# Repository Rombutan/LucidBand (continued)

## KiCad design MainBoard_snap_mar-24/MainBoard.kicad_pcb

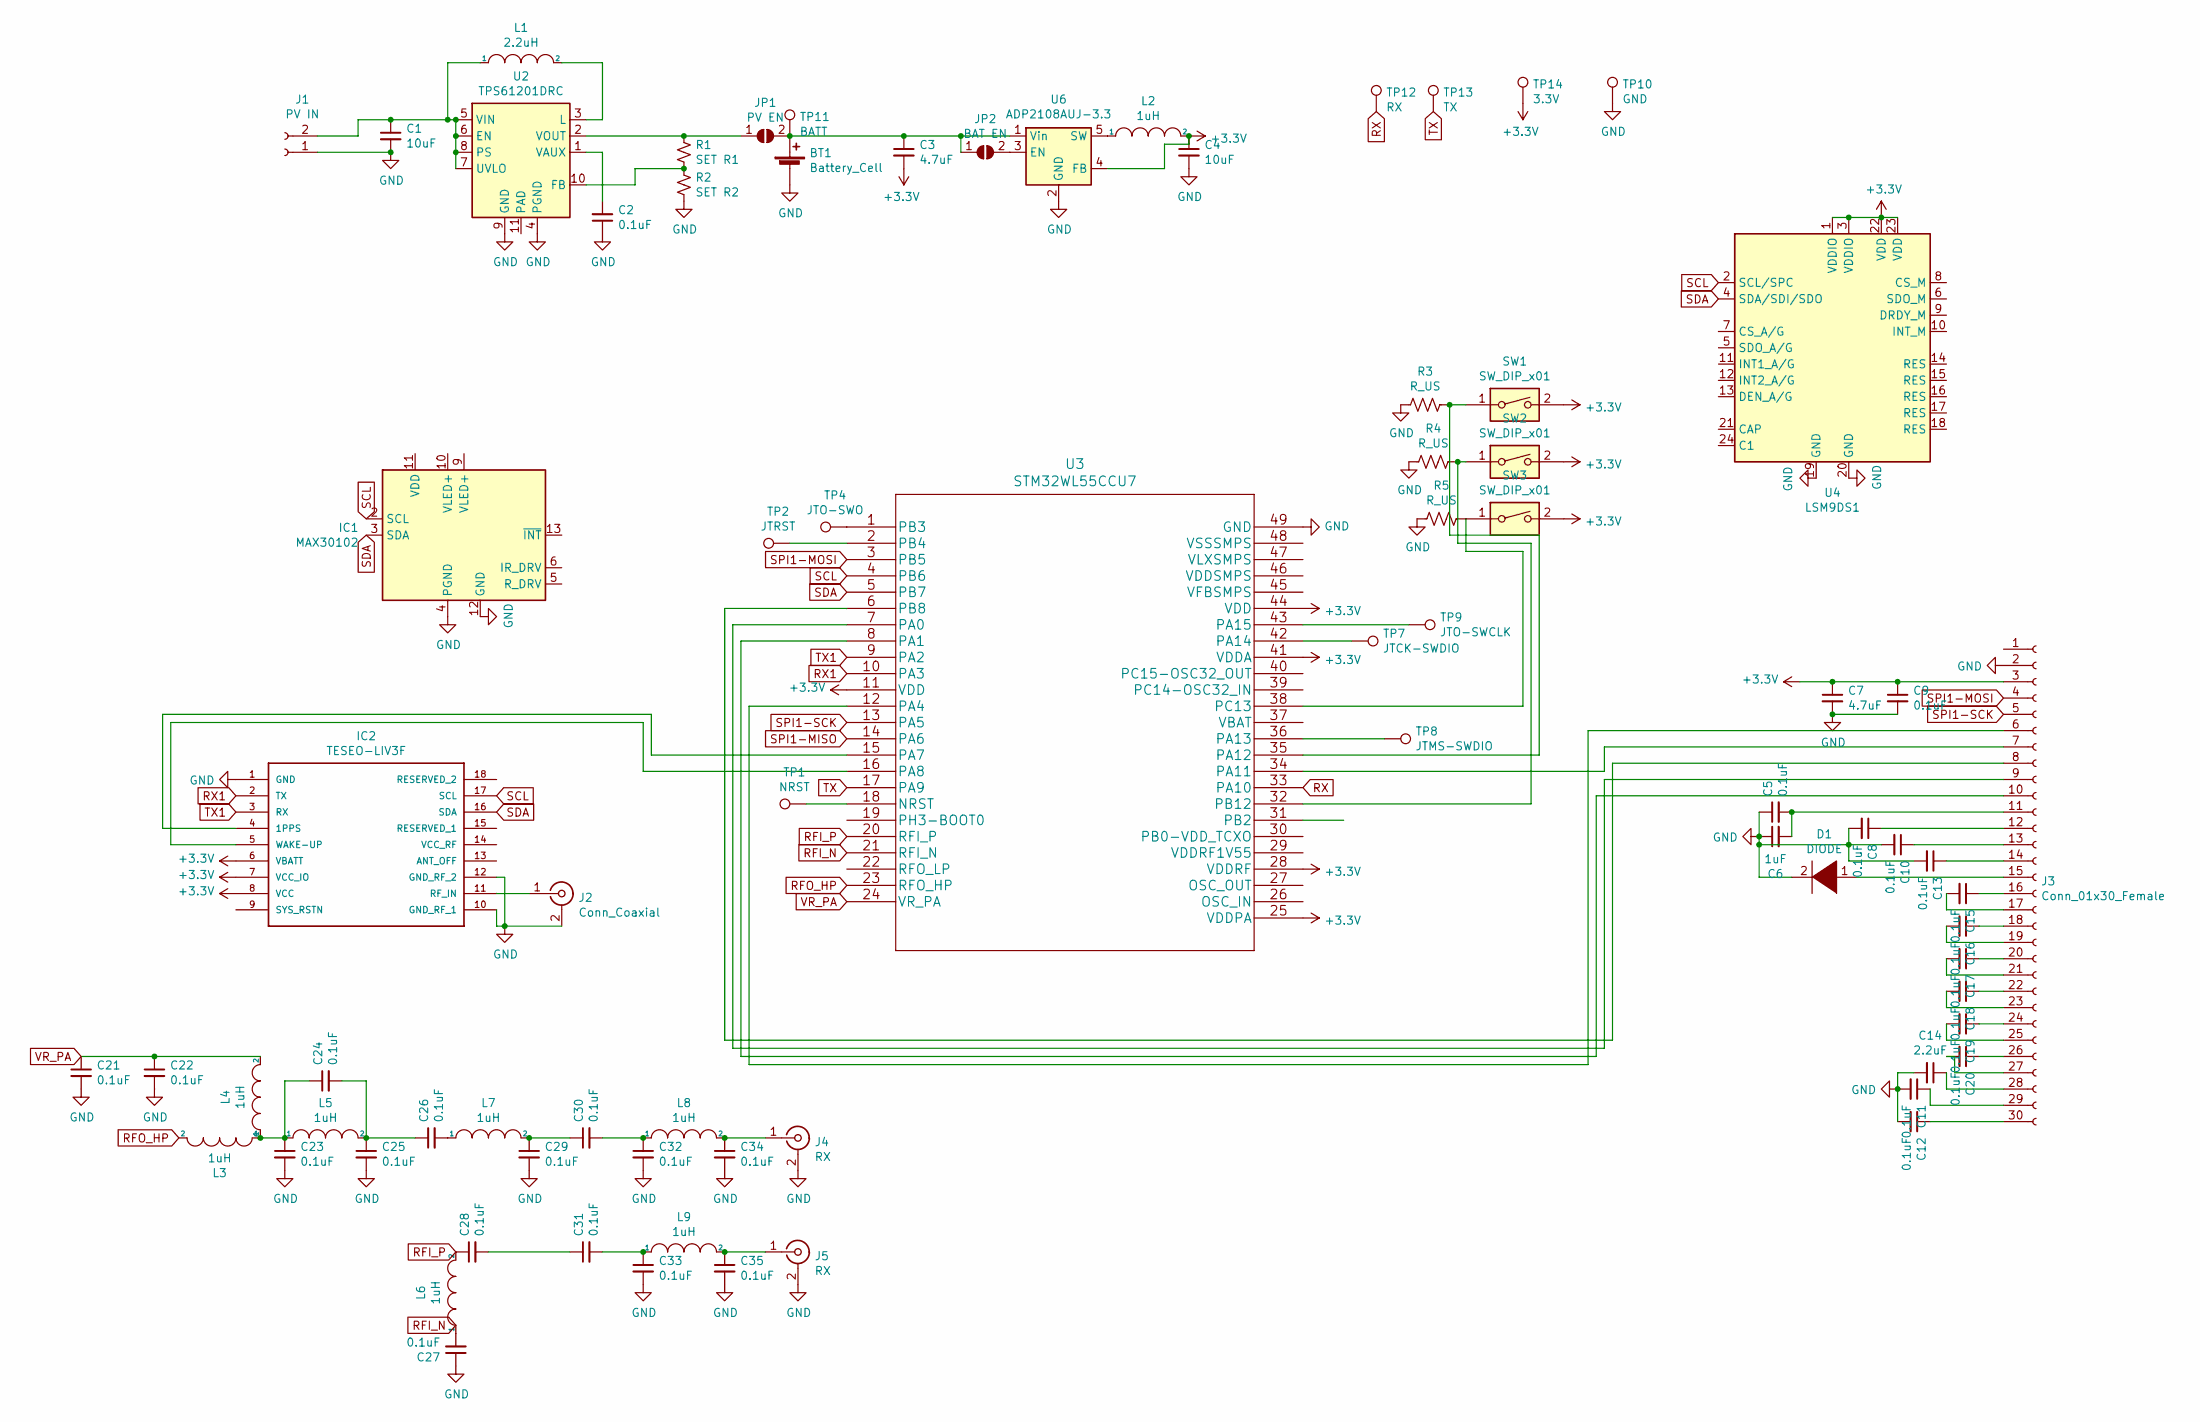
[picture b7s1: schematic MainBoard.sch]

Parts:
BT1: Battery_Cell; PinHeader_1x02_P1.00mm_Horizontal
C1, C4: 10uF; C_0402_1005Metric
C2, C5, C8, C9, C10, C11, C12, C13, C15, C16, C17, C18, C19, C20, C21, C22, C23, C24, C25, C26, C27, C28, C29, C30, C31, C32, C33, C34, C35: 0.1uF; C_0402_1005Metric
C3, C7: 4.7uF; C_0402_1005Metric
C6: 1uF; C_0402_1005Metric
C14: 2.2uF; C_0402_1005Metric
D1: DIODE; D_0402_1005Metric
IC1: MAX30102; Maxim_OLGA-14_3.3x5.6mm_P0.8mm
IC2: TESEO-LIV3F; SON110P970X1010X230-18N; MOUSER_PART_NUMBER 511-TESEO-LIV3F
J1: PV IN; PinHeader_1x02_P1.00mm_Horizontal
J2: Conn_Coaxial; U.FL_Hirose_U.FL-R-SMT-1_Vertical
J3: Conn_01x30_Female; waveshare_1.02
J4, J5: RX; U.FL_Hirose_U.FL-R-SMT-1_Vertical
JP1: PV EN; SolderJumper-2_P1.3mm_Open_RoundedPad1.0x1.5mm
JP2: BAT EN; SolderJumper-2_P1.3mm_Open_RoundedPad1.0x1.5mm
L1: 2.2uH; L_Coilcraft_LPS4018
L2: 1uH; L_Coilcraft_LPS4018
L3, L4, L5, L6, L7, L8, L9: 1uH; L_0402_1005Metric
R1: SET R1; R_0402_1005Metric
R2: SET R2; R_0402_1005Metric
R3, R4, R5: R_US; R_0402_1005Metric
SW1, SW2, SW3: SW_DIP_x01; SW_Push_1P1T-SH_NO_CK_KMR2xxG
TP1: NRST; TestPoint_Pad_2.0x2.0mm
TP2: JTRST; TestPoint_Pad_2.0x2.0mm
TP4: JTO-SWO; TestPoint_Pad_2.0x2.0mm
TP7: JTCK-SWDIO; TestPoint_Pad_2.0x2.0mm
TP8: JTMS-SWDIO; TestPoint_Pad_2.0x2.0mm
TP9: JTO-SWCLK; TestPoint_Pad_2.0x2.0mm
TP10: GND; TestPoint_Pad_2.0x2.0mm
TP11: BATT; TestPoint_Pad_2.0x2.0mm
TP12: RX; TestPoint_Pad_2.0x2.0mm
TP13: TX; TestPoint_Pad_2.0x2.0mm
TP14: 3.3V; TestPoint_Pad_2.0x2.0mm
U2: TPS61201DRC; Texas_S-PVSON-N10_ThermalVias
U3: STM32WL55CCU7
U4: LSM9DS1; LGA-24L_3x3.5mm_P0.43mm
U6: ADP2108AUJ-3.3; TSOT-23-5

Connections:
+3V3: C3.2, C4.1, C7.1, C9.1, IC2.6 (VBATT), IC2.7 (VCC_IO), IC2.8 (VCC), J3.3, L2.2, SW1.2, SW2.2, SW3.2, TP14.1, U3.11 (VDD), U3.25 (VDDPA), U3.28 (VDDRF), U3.41 (VDDA), U3.44 (VDD), U4.1 (VDDIO), U4.3 (VDDIO), U4.22 (VDD), U4.23 (VDD), U6.4 (FB)
GND: BT1.2 (-), C1.2, C2.1, C4.2, C5.1, C6.1, C7.2, C8.2, C9.2, C10.2, C11.2, C12.2, C13.2, C14.2, C21.2, C22.2, C23.2, C25.2, C27.1, C29.2, C32.2, C33.2, C34.2, C35.2, D1.2 (A), IC1.4 (PGND), IC1.12 (GND), IC2.1 (GND), IC2.10 (GND_RF_1), IC2.12 (GND_RF_2), J1.1, J2.2 (Ext), J3.2, J4.2 (Ext), J5.2 (Ext), R2.2, R3.2, R4.2, R5.2, TP10.1, U2.4 (PGND), U2.9 (GND), U3.49 (GND), U4.19 (GND), U4.20 (GND), U6.2 (GND)
unnamed: BT1.1 (+), C3.1, JP1.2 (B), JP2.1 (A), TP11.1, U6.1 (Vin)
unnamed: C1.1, J1.2, L1.1, U2.5 (VIN), U2.6 (EN), U2.7 (UVLO), U2.8 (PS)
unnamed: C2.2, U2.1 (VAUX)
unnamed: C5.2, C6.2, J3.11
unnamed: C8.1, J3.12
unnamed: C10.1, J3.13
unnamed: C11.1, J3.29
unnamed: C12.1, J3.30
unnamed: C13.1, J3.14
unnamed: C14.1, J3.28
unnamed: C15.1, J3.16
unnamed: C15.2, J3.17
unnamed: C16.1, J3.18
unnamed: C16.2, J3.19
unnamed: C17.1, J3.20
unnamed: C17.2, J3.21
unnamed: C18.1, J3.22
unnamed: C18.2, J3.23
unnamed: C19.1, J3.24
unnamed: C19.2, J3.25
unnamed: C20.1, J3.26
unnamed: C20.2, J3.27
unnamed: C23.1, C24.1, L3.1, L4.1, L5.1
unnamed: C24.2, C25.1, C26.1, L5.2
unnamed: C26.2, L7.1
unnamed: C27.2, L6.1
unnamed: C28.2, C31.1
unnamed: C29.1, C30.1, L7.2
unnamed: C30.2, C32.1, L8.1
unnamed: C31.2, C33.1, L9.1
unnamed: C34.1, J4.1 (In), L8.2
unnamed: C35.1, J5.1 (In), L9.2
unnamed: D1.1 (K), J3.15
unnamed: IC2.4 (1PPS), U3.15 (PA7)
unnamed: IC2.5 (WAKE-UP), U3.16 (PA8)
unnamed: IC2.11 (RF_IN), J2.1 (In)
unnamed: J3.6, U3.12 (PA4)
unnamed: J3.7, U3.34 (PA11)
unnamed: J3.8, U3.6 (PB8)
unnamed: J3.9, U3.7 (PA0)
unnamed: J3.10, U3.8 (PA1)
unnamed: JP1.1 (A), R1.1, U2.2 (VOUT)
unnamed: JP2.2 (B), U6.3 (EN)
unnamed: L1.2, U2.3 (L)
unnamed: L2.1, U6.5 (SW)
unnamed: R1.2, R2.1, U2.10 (FB)
unnamed: R3.1, SW1.1, U3.35 (PA12)
unnamed: R4.1, SW2.1, U3.32 (PB12)
unnamed: R5.1, SW3.1, U3.38 (PC13)
unnamed: TP1.1, U3.18 (NRST)
unnamed: TP2.1, U3.2 (PB4)
unnamed: TP4.1, U3.1 (PB3)
unnamed: TP7.1, U3.42 (PA14)
unnamed: TP8.1, U3.36 (PA13)
unnamed: TP9.1, U3.43 (PA15)
RFI_P: C28.1, L6.2, U3.20 (RFI_P)
RFO_HP: L3.2, U3.23 (RFO_HP)
RX: TP12.1, U3.33 (PA10)
RX1: IC2.2 (TX), U3.10 (PA3)
SCL: IC1.2 (SCL), IC2.17 (SCL), U3.4 (PB6), U4.2 (SCL/SPC)
SDA: IC1.3 (SDA), IC2.16 (SDA), U3.5 (PB7), U4.4 (SDA/SDI/SDO)
SPI1-MOSI: J3.4, U3.3 (PB5)
SPI1-SCK: J3.5, U3.13 (PA5)
TX: TP13.1, U3.17 (PA9)
TX1: IC2.3 (RX), U3.9 (PA2)
VR_PA: C21.1, C22.1, L4.2, U3.24 (VR_PA)

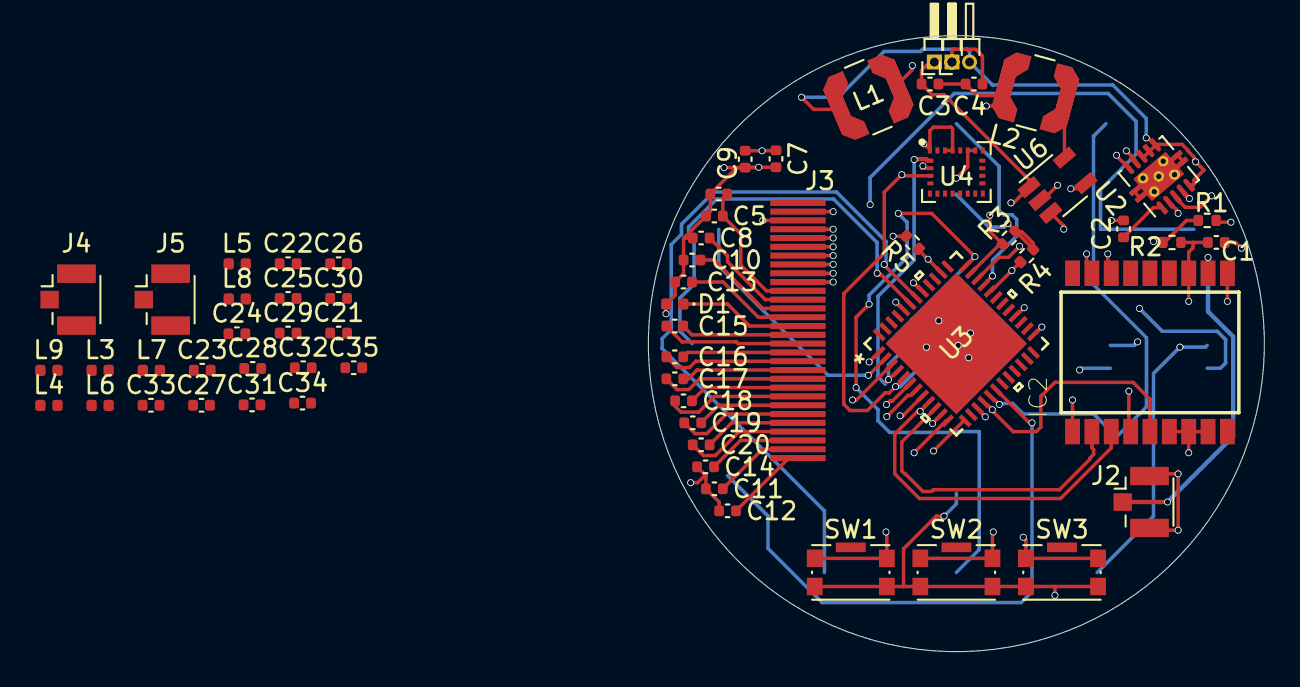
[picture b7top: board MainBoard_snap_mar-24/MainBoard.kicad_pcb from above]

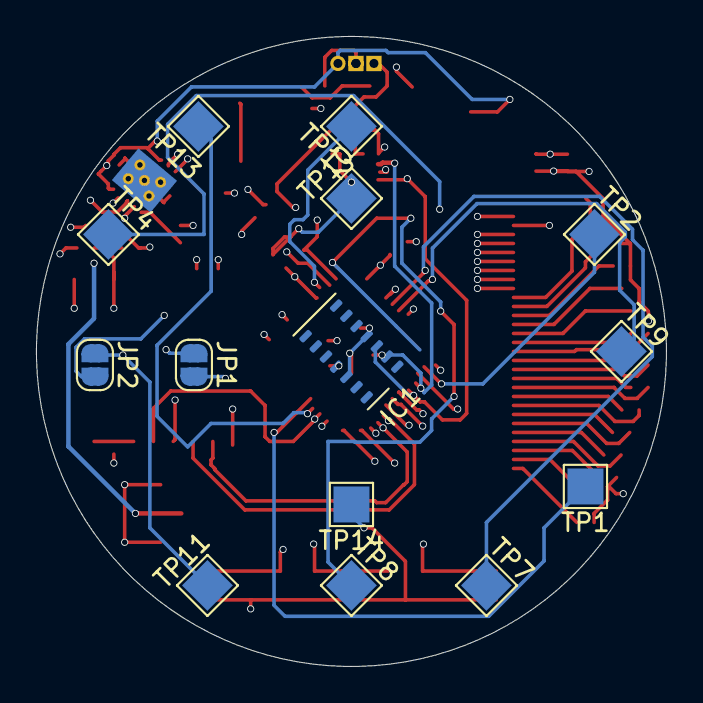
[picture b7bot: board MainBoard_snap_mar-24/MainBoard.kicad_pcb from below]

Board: 4 copper layers, 35.0 x 35.0 mm, 78 parts (14 on the bottom side), 68 nets.

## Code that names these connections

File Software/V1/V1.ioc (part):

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PA10.Mode=Asynchronous
Mcu.UserName=STM32WL55CCUx
PC14-OSC32_IN.Signal=GPIO_Output
PA3.Mode=Asynchronous
PA13.Signal=DEBUG_JTMS-SWDIO
PA9.Mode=Asynchronous
PA9.Signal=USART1_TX
PB6.Signal=I2C1_SCL
PB6.Mode=I2C
PC15-OSC32_OUT.Signal=GPIO_Input
PA1.Signal=GPIO_Output
RCC.HSE_VALUE=8000000
PB3.Mode=JTAG_5_pins
PB2.Signal=GPIO_Output
board=custom
PA15.Mode=JTAG_5_pins
PB4.Mode=JTAG_5_pins
PA14.Mode=JTAG_5_pins
PB7.Signal=I2C1_SDA
PA8.Signal=GPIO_Output
PA13.Mode=JTAG_5_pins
Mcu.Name=STM32WL55CCUx
PA2.Signal=USART2_TX
PA0.Signal=GPIO_Output
PB3.Signal=DEBUG_JTDO-SWO
PA4.Signal=GPIO_Output
Mcu.Package=UFQFPN48
PA11.Signal=GPIO_Output
PB7.Mode=I2C
PA10.Signal=USART1_RX
PA14.Signal=DEBUG_JTCK-SWCLK
PA15.Signal=DEBUG_JTDI
PB8.Signal=GPIO_Output
PA2.Mode=Asynchronous
PB4.Signal=DEBUG_JTRST
PA3.Signal=USART2_RX
PA7.Signal=GPIO_Output

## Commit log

2021-03-21 add sensors.txt
2021-03-21 add mainboard PCB files
2021-03-22 add PV supply circuit
2021-03-24 add final sensors and update PCB
2021-03-26 lots of work on PCB
2021-03-28 clean silkscreen, add power delivery, route LoRa RF
2021-03-28 add pdfs
2021-03-28 flip LoRa TX stuff to deduce footprint and track length, update pdfs
2021-03-31 ditch LoRa, switch processor to STM32WB30CE
2021-03-31 route entire damn thing in one sitting
2021-03-31 add crystal, pour ground plane
2021-05-06 many, many things :)
2021-05-06 add programming/charging dock board
2021-05-07 export gerbers
2021-05-17 remove old layout pdf
2021-05-18 add accelerometer and thicken switch traces
2021-05-18 Update images
2021-05-22 I dont even remember
2021-05-30 switch processor, add sensors, change shape'
2021-05-31 update pdf's
2021-05-31 remove old stuffs
2021-05-31 update images for README
2021-05-31 oops! I forgot the buzzer
2021-06-04 route board
2021-06-04 update 3d image
2023-01-05 make readme and decide hardware
2023-01-05 fix list in README
2023-01-05 goofy submodule won't die
2023-01-05 init pcb commit
2023-01-05 finish schematic
2023-01-05 preliminary layout
2023-01-06 finish layout and route
2023-01-06 v1 final changes
